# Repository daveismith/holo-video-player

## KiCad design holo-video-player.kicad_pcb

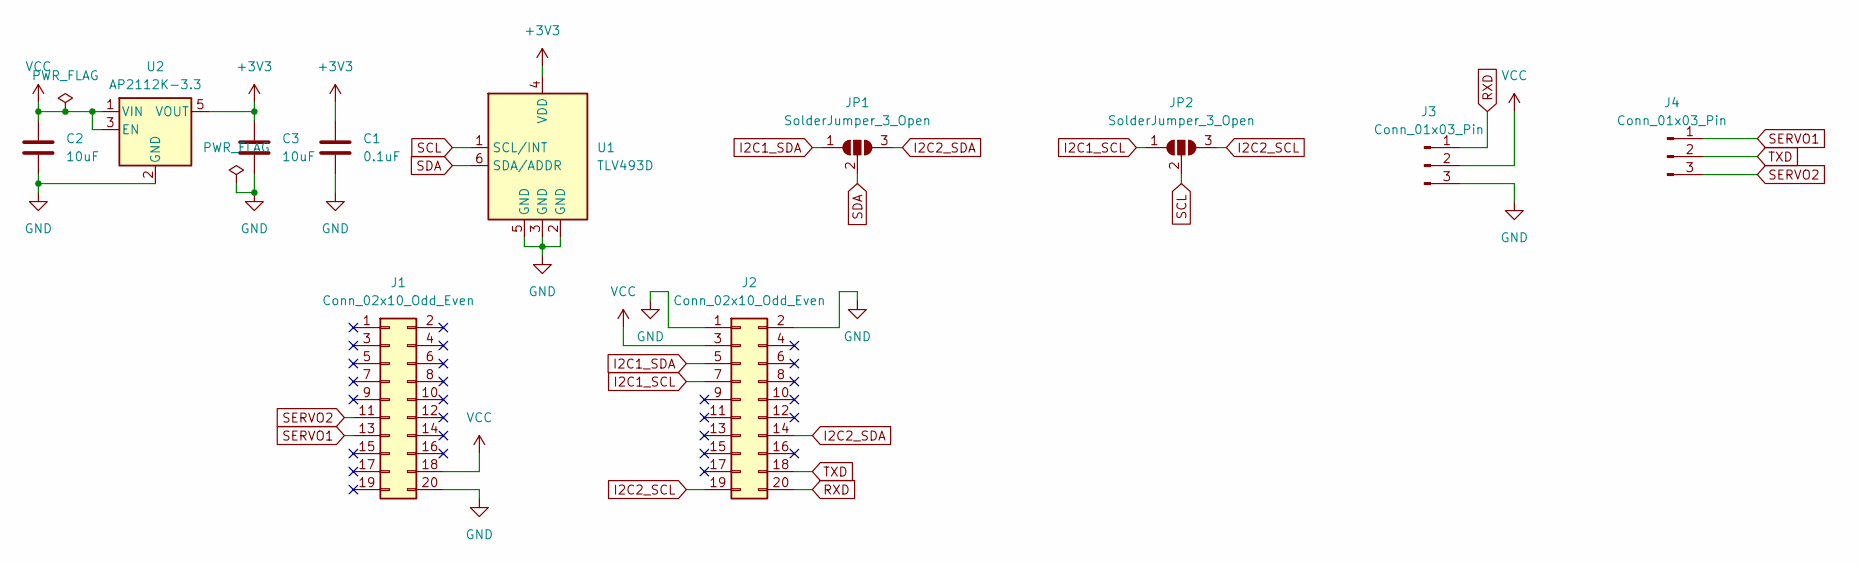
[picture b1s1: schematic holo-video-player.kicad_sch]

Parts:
C1: 0.1uF; C_0402_1005Metric; JLCPCB C14663
C2, C3: 10uF; C_0603_1608Metric; JLCPCB C96446
J1, J2: Conn_02x10_Odd_Even; PinHeader_2x10_P1.27mm_Vertical
J3, J4: Conn_01x03_Pin; JST_SH_SM03B-SRSS-TB_1x03-1MP_P1.00mm_Horizontal; JLCPCB C160403
JP1, JP2: SolderJumper_3_Open; SolderJumper-3_P1.3mm_Open_RoundedPad1.0x1.5mm
U1: TLV493D; SOT-23-6; JLCPCB C126688
U2: AP2112K-3.3; SOT-23-5; JLCPCB C51118

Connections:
+3V3: C1.1, C3.1, U1.4 (VDD), U2.5 (VOUT)
GND: C1.2, C2.2, C3.2, J1.20, J2.1, J2.2, J3.3, U1.2 (GND), U1.3 (GND), U1.5 (GND), U2.2 (GND)
I2C1_SCL: J2.7, JP2.1 (A)
I2C1_SDA: J2.5, JP1.1 (A)
I2C2_SCL: J2.19, JP2.3 (B)
I2C2_SDA: J2.14, JP1.3 (B)
RXD: J2.20, J3.1
SCL: JP2.2 (C), U1.1 (SCL/INT)
SDA: JP1.2 (C), U1.6 (SDA/ADDR)
SERVO1: J1.13, J4.1
SERVO2: J1.11, J4.3
TXD: J2.18, J4.2
VCC: C2.1, J1.18, J2.3, J3.2, U2.1 (VIN), U2.3 (EN)

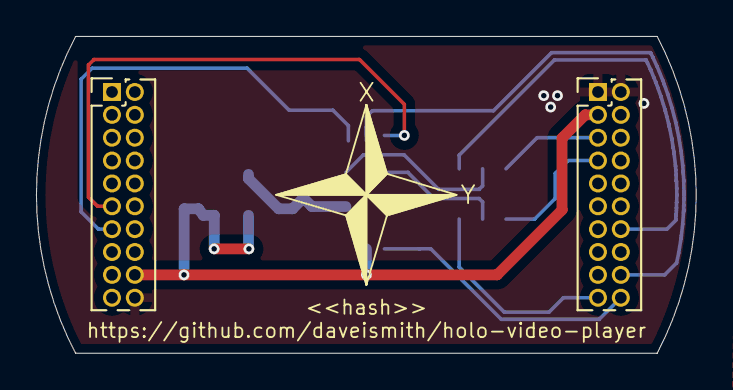
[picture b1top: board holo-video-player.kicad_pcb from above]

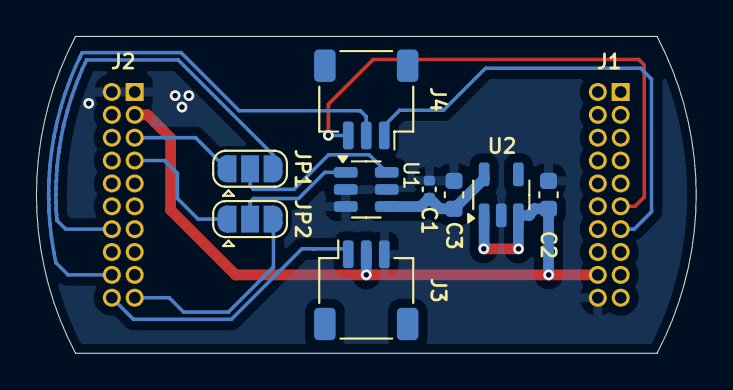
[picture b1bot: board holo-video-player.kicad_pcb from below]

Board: 2 copper layers, 36.7 x 17.6 mm, 11 parts (9 on the bottom side), 13 nets.

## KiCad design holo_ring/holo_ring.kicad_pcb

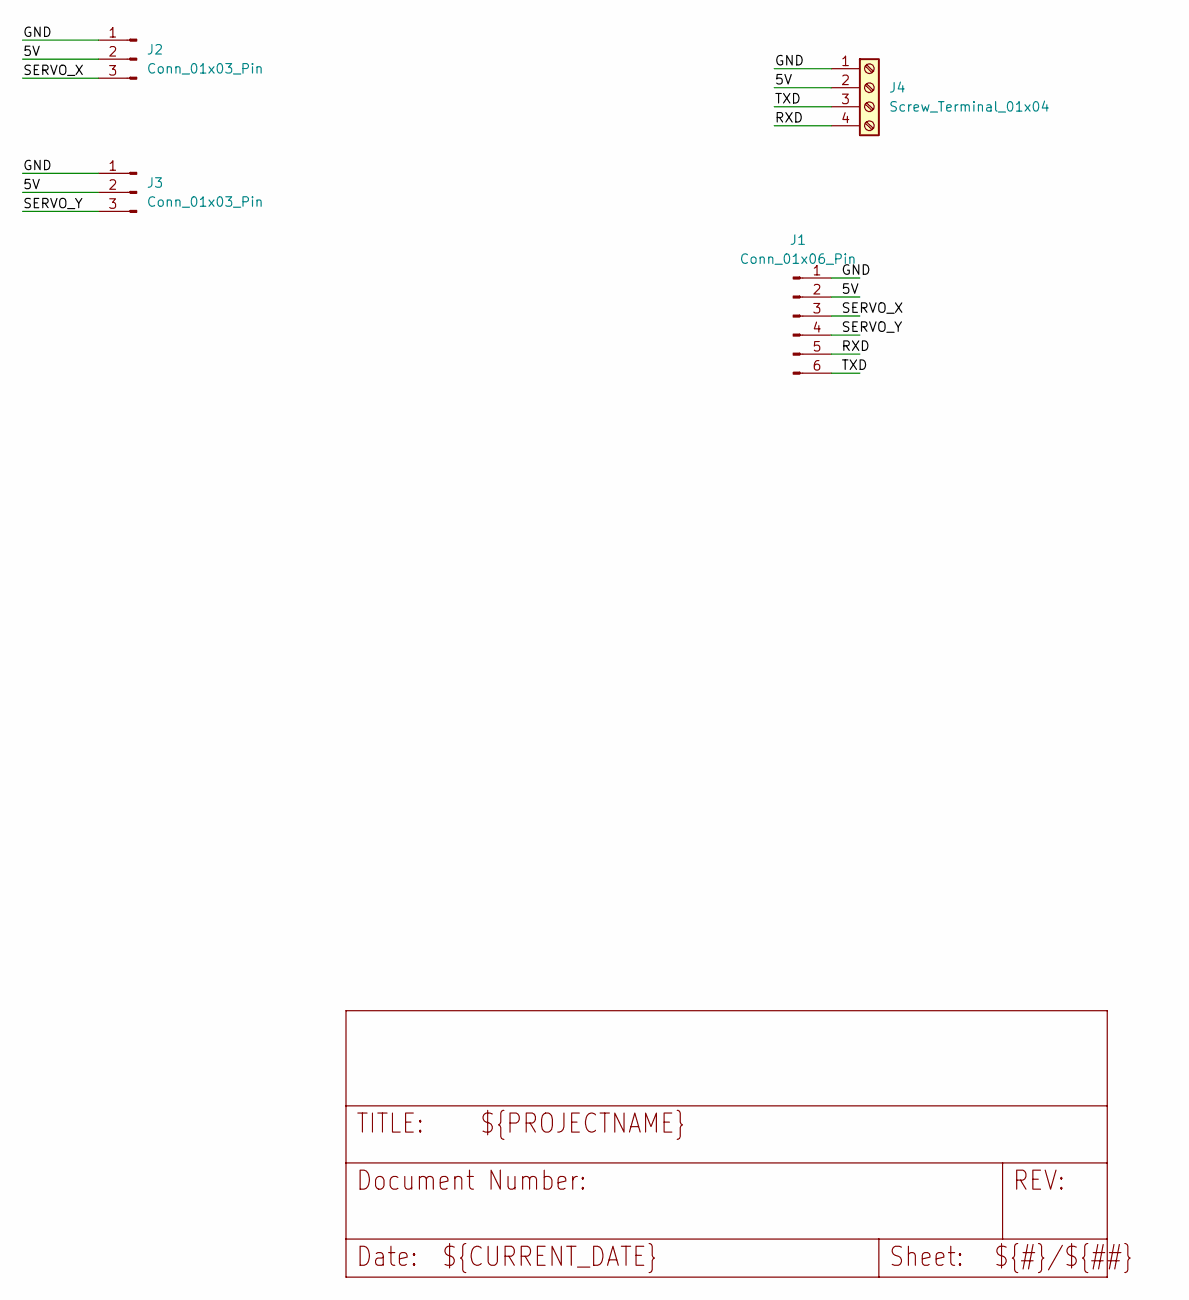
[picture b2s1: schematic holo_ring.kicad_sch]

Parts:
J1: Conn_01x06_Pin; JST_SH_SM06B-SRSS-TB_1x06-1MP_P1.00mm_Horizontal
J2, J3: Conn_01x03_Pin; PinHeader_1x03_P2.54mm_Vertical
J4: Screw_Terminal_01x04; TerminalBlock_TE_282834-4_1x04_P2.54mm_Horizontal

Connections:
/5V: J1.2, J2.2, J3.2, J4.2
/GND: J1.1, J2.1, J3.1, J4.1
/RXD: J1.5, J4.4
/SERVO_X: J1.3, J2.3
/SERVO_Y: J1.4, J3.3
/TXD: J1.6, J4.3

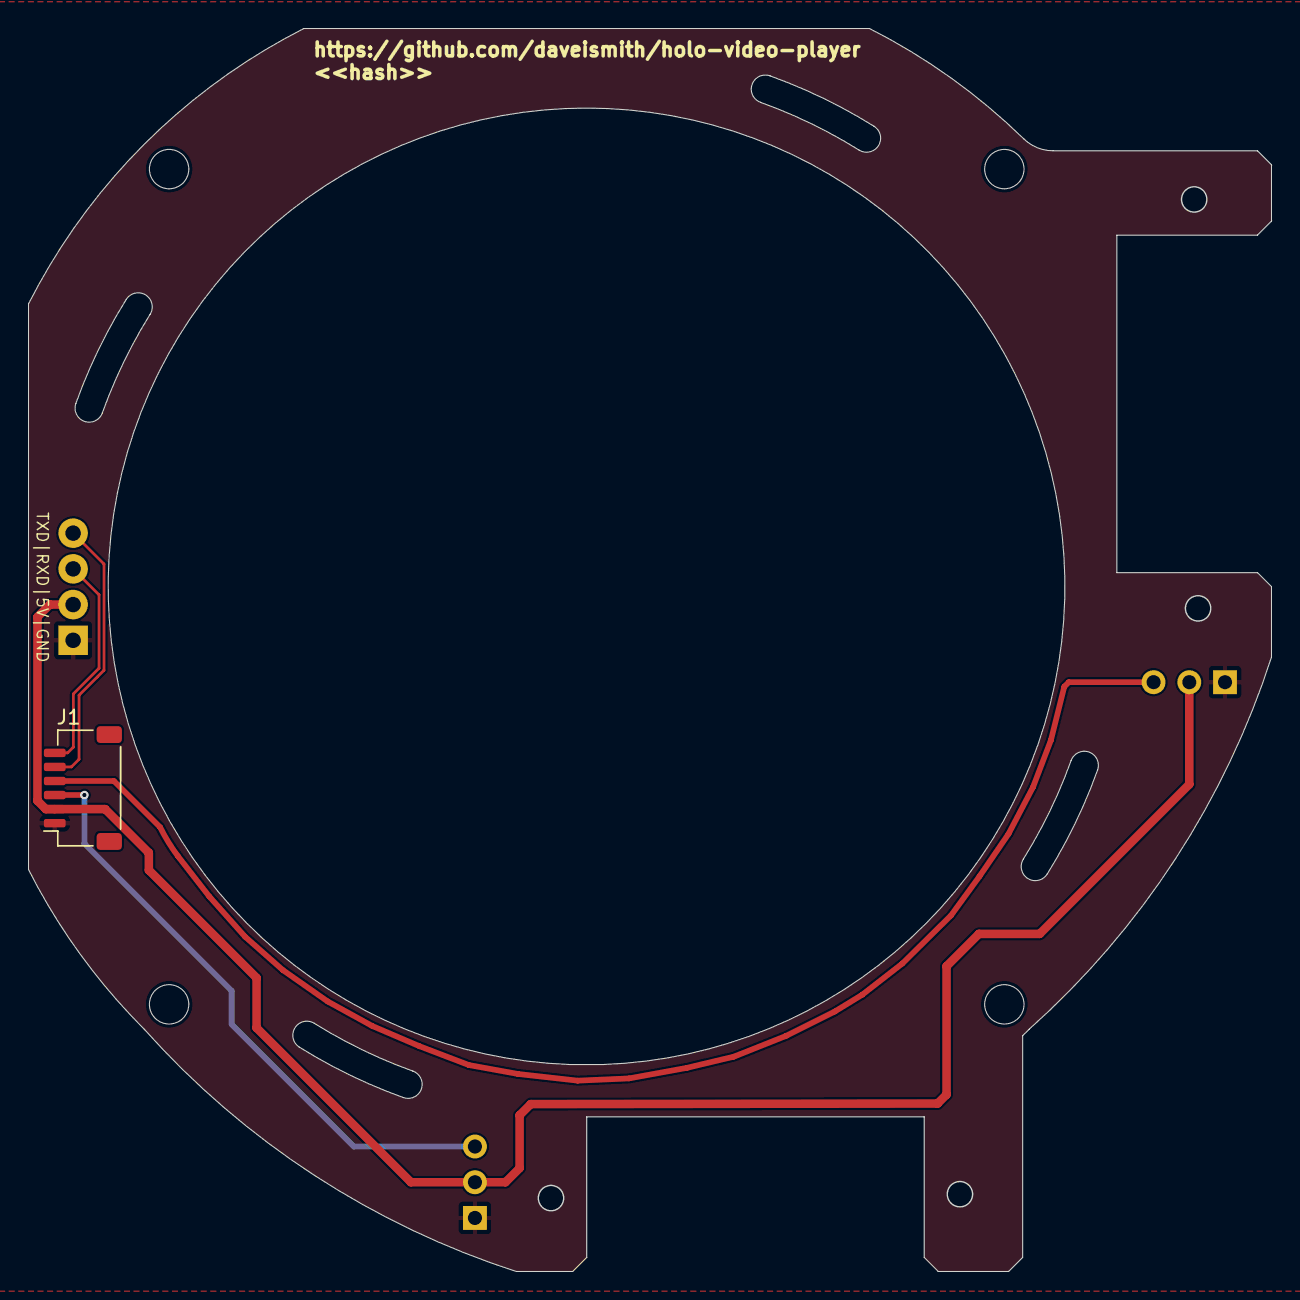
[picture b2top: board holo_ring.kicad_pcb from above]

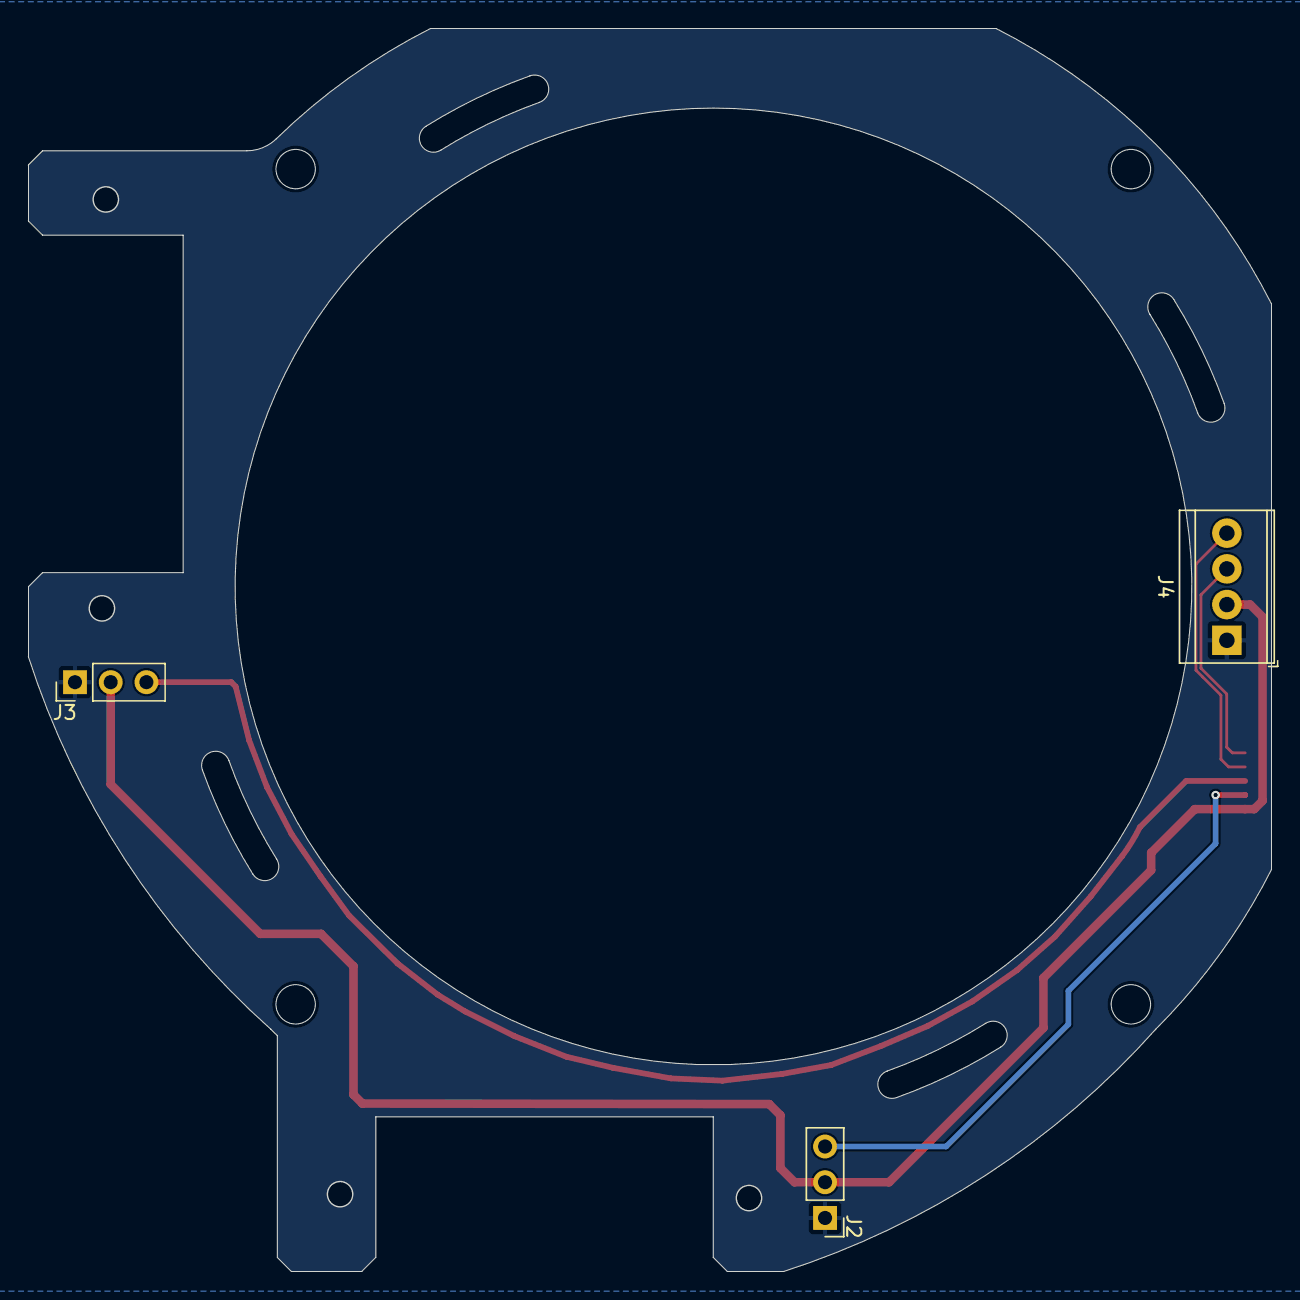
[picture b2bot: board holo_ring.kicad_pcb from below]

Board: 2 copper layers, 88.3 x 88.3 mm, 8 parts (3 on the bottom side), 6 nets.

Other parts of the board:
@HOLE0, @HOLE1, @HOLE2, @HOLE3: (no value)

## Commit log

2024-07-15 Updates to make hash work in for all PCB files instead of specifying the specific file.
2024-07-15 Switching from 4-layer to 2-layer export config
2024-07-15 Adding JLCPCB Part Registrations.
2024-07-22 Adding outer ring for Holo Projector
2024-07-22 Correcting part number on Holo Video Player Board
